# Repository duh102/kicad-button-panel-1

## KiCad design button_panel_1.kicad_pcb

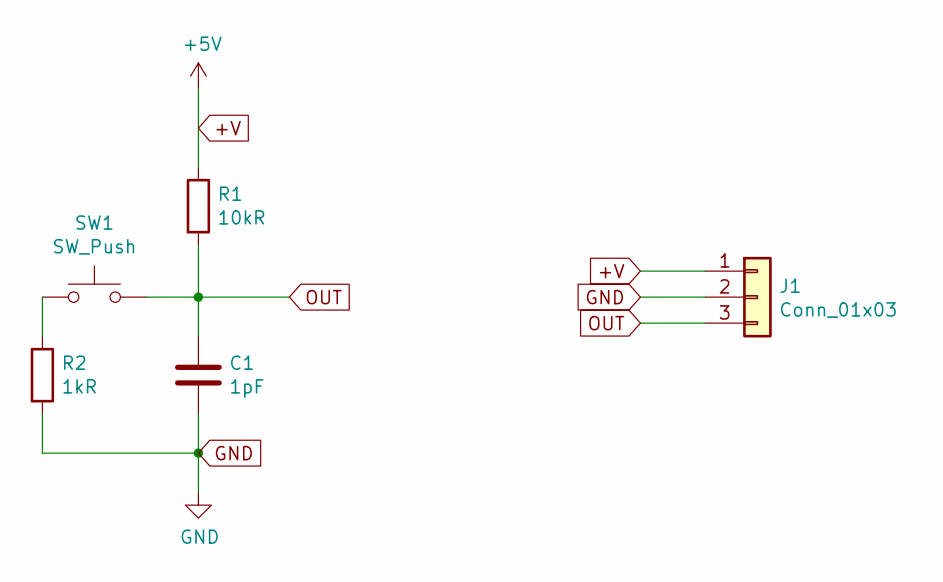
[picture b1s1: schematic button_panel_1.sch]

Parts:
C1: 1pF; C_0805_2012Metric
J1: Conn_01x03; PinHeader_1x03_P2.54mm_Vertical
R1: 10kR; R_0805_2012Metric
R2: 1kR; R_0805_2012Metric
SW1: SW_Push; SW_Push_1P1T_NO_CK_KMR2

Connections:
+V: J1.1, R1.1
GND: C1.2, J1.2, R2.2
unnamed: R2.1, SW1.1
OUT: C1.1, J1.3, R1.2, SW1.2

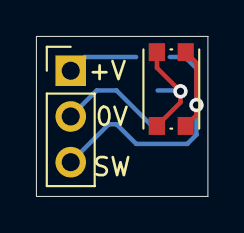
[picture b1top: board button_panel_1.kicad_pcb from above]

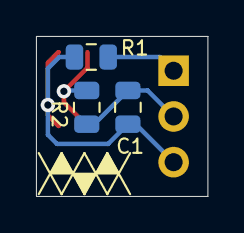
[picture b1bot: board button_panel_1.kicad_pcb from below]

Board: 2 copper layers, 9.5 x 8.9 mm, 5 parts (3 on the bottom side), 4 nets.
